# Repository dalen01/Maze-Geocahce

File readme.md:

# Maze Geocache

An electronic maze puzzle inspired by the maze module in *Keep Talking and Nobody Explodes*. A player uses an arcade joystick to move a white light through an invisible maze on a 6×6 RGB LED matrix. Reaching four randomly selected goals in succession triggers a solenoid and opens the geocache.

This repository contains the Arduino firmware, KiCad PCB design and production files, enclosure models, and laser-cutting drawings required to build the project.

## How it works

- The two green LEDs identify which of the nine maze layouts is active.
- The white LED is the player's current position.
- The red LED is the goal.
- The joystick moves the player up, down, left, or right.
- Hitting a wall or the edge of the matrix displays a red cross and resets progress.
- Reaching a goal displays the number of rounds remaining and loads a new random maze.
- Completing four mazes plays a victory animation and energizes the solenoid for 500 ms.

The walls are intentionally not shown on the LED matrix. Players must use an external maze reference or solve the layout by deduction.

## Hardware

The supplied PCB is designed around the following main components:

- Arduino Nano or a pin-compatible board
- 36 × WS2812B addressable RGB LEDs arranged as a 6×6 matrix
- Arcade joystick with four directional switches
- Solenoid lock
- TIP120 Darlington transistor and SS34 flyback diode for solenoid control
- 3 × AA battery holder
- Custom PCB and enclosure

See [`PCB Design/Maze Geocache/production/bom.csv`](PCB%20Design/Maze%20Geocache/production/bom.csv) for the PCB bill of materials and component footprints.

## Pin assignment

| Function | Arduino Nano pin |
| --- | ---: |
| Solenoid control | D2 |
| Joystick up | D3 |
| Joystick down | D4 |
| Joystick right | D5 |
| Joystick left | D6 |
| WS2812B data | D7 |

The directional inputs use the Arduino's internal pull-up resistors and are active low.

## Firmware setup

### Requirements

- Arduino IDE or Arduino CLI
- Arduino AVR Boards package
- [Adafruit NeoPixel](https://github.com/adafruit/Adafruit_NeoPixel) library

### Prepare the sketch

The current sketch contains an absolute Windows path for `MazeWalls.h`. Before compiling on another computer:

1. Copy `Code/MazeWalls.h` into `Code/Maze/`.
2. Change the second line of `Code/Maze/Maze.ino` to:

```cpp
#include "MazeWalls.h"
```

### Upload with Arduino IDE

1. Open `Code/Maze/Maze.ino`.
2. Install **Adafruit NeoPixel** from the Library Manager.
3. Select **Arduino Nano** and the correct processor variant and serial port.
4. Compile and upload the sketch.
5. Optionally open the Serial Monitor at **9600 baud** to view movement and game-state messages.

## Assembly notes

1. Manufacture and populate the PCB from the files in `PCB Design/Maze Geocache/`.
2. Connect the four joystick switches to the matching UP, DOWN, LEFT, and RIGHT JST connectors.
3. Connect the solenoid to the two-pin screw terminal.
4. Install the Arduino Nano with the correct orientation.
5. Fit the PCB, joystick, lock, and battery holder into the enclosure.
6. Test all controls and the lock release before closing the enclosure.

The solenoid is an inductive, relatively high-current load. Do not drive it directly from an Arduino pin. Confirm the solenoid voltage, polarity, current requirement, transistor pinout, flyback-diode orientation, and power-source capability before applying power.

## Repository layout

| Path | Contents |
| --- | --- |
| `Code/` | Arduino sketch and maze wall definitions |
| `PCB Design/` | KiCad schematics, PCB layout, 3D board model, BOM, placement data, and fabrication archive |
| `3D Files/` | Fusion 360 archive and STEP model of the complete enclosure |
| `DXF Files/` | Laser-cutting drawings for the box and acrylic window |

## Customization

- Change `numberToGo` in `Maze.ino` to alter the number of successful mazes required to unlock the cache.
- Adjust the RGB values in `drawGame()` to change marker colors or brightness.
- Edit `circlePos`, `wallsVertical`, and `wallsHorizontal` in `MazeWalls.h` to change or add maze layouts. Update `MAZE_COUNT` when adding or removing layouts.
- Change the 500 ms delay in the victory sequence if the lock needs a different activation time, while staying within the solenoid's safe duty cycle.

## Fabrication warning

Review the PCB, mechanical files, clearances, power design, and production outputs before ordering parts or manufacturing. The repository does not include a verified electrical rating for the solenoid or batteries, and the design files should not be treated as production-ready without an independent check.

## Acknowledgements

The puzzle concept is inspired by the maze module from *Keep Talking and Nobody Explodes*. This is an independent fan project and is not affiliated with or endorsed by Steel Crate Games.

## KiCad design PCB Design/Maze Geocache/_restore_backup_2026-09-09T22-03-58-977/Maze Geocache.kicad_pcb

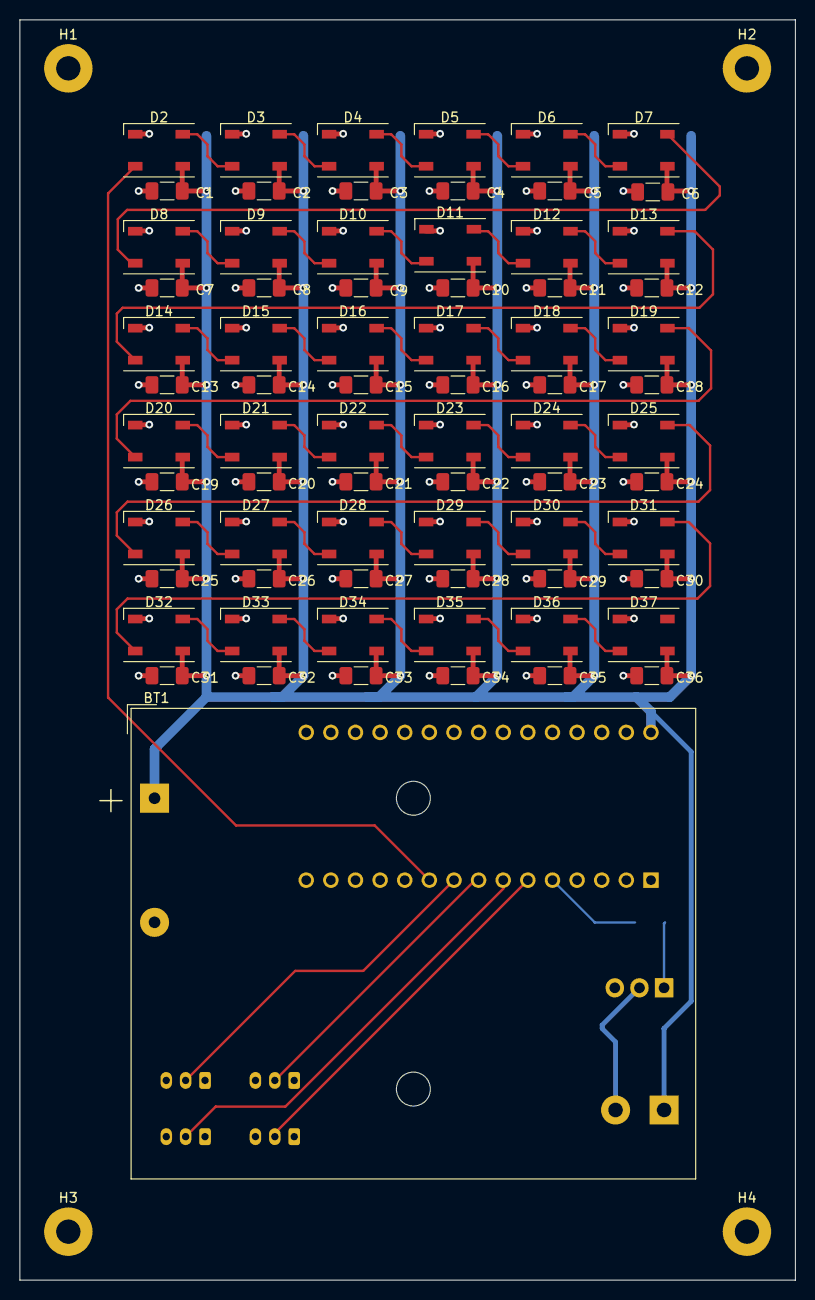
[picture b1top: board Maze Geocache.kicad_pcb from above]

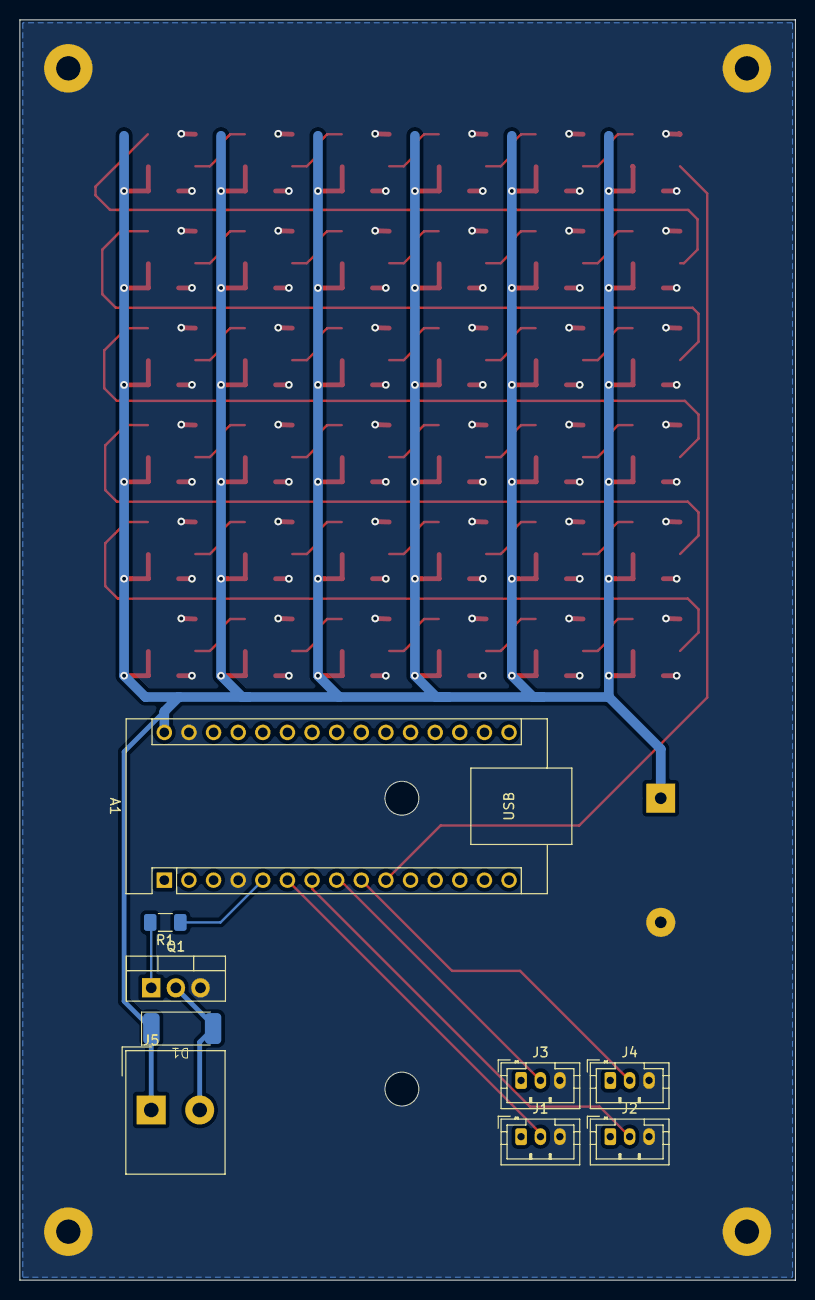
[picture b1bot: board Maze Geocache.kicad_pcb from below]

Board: 2 copper layers, 80.0 x 130.0 mm, 86 parts (9 on the bottom side), 45 nets.

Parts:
A1: Arduino_Nano_v2.x; Arduino_Nano
BT1: Battery; BatteryHolder_TruPower_BH-331P_3xAA
C1, C2, C3, C4, C5, C6, C7, C8, C9, C10, C11, C12, C13, C14, C15, C16, C17, C18, C19, C20, C21, C22, C23, C24, C25, C26, C27, C28, C29, C30, C31, C32, C33, C34, C35, C36: 10pF; C_1206_3216Metric_Pad1.33x1.80mm_HandSolder
D1: SS34
D2, D3, D4, D5, D6, D7, D8, D9, D10, D11, D12, D13, D14, D15, D16, D17, D18, D19, D20, D21, D22, D23, D24, D25, D26, D27, D28, D29, D30, D31, D32, D33, D34, D35, D36, D37: WS2812B; LED_WS2812B_PLCC4_5.0x5.0mm_P3.2mm
H1, H2, H3, H4: MountingHole_Pad; MountingHole_2.5mm_Pad
J1: Joystick connector UP; JST_PH_B3B-PH-K_1x03_P2.00mm_Vertical
J2: Joystick connector DOWN; JST_PH_B3B-PH-K_1x03_P2.00mm_Vertical
J3: Joystick connector RIGHT; JST_PH_B3B-PH-K_1x03_P2.00mm_Vertical
J4: Joystick connector LEFT; JST_PH_B3B-PH-K_1x03_P2.00mm_Vertical
J5: Solenoid; Altech_AK300_1x02_P5.00mm_45-Degree
Q1: TIP120; TO-220-3_Vertical
R1: 220; R_1206_3216Metric_Pad1.30x1.75mm_HandSolder

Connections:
+5V: A1.30 (VIN), BT1.1 (+), C1.2, C2.2, C3.2, C4.2, C5.2, C6.2, C7.2, C8.2, C9.2, C10.2, C11.2, C12.2, C13.2, C14.2, C15.2, C16.2, C17.2, C18.2, C19.2, C20.2, C21.2, C22.2, C23.2, C24.2, C25.2, C26.2, C27.2, C28.2, C29.2, C30.2, C31.2, C32.2, C33.2, C34.2, C35.2, C36.2, D1.2, D2.1 (VDD), D3.1 (VDD), D4.1 (VDD), D5.1 (VDD), D6.1 (VDD), D7.1 (VDD), D8.1 (VDD), D9.1 (VDD), D10.1 (VDD), D11.1 (VDD), D12.1 (VDD), D13.1 (VDD), D14.1 (VDD), D15.1 (VDD), D16.1 (VDD), D17.1 (VDD), D18.1 (VDD), D19.1 (VDD), D20.1 (VDD), D21.1 (VDD), D22.1 (VDD), D23.1 (VDD), D24.1 (VDD), D25.1 (VDD), D26.1 (VDD), D27.1 (VDD), D28.1 (VDD), D29.1 (VDD), D30.1 (VDD), D31.1 (VDD), D32.1 (VDD), D33.1 (VDD), D34.1 (VDD), D35.1 (VDD), D36.1 (VDD), D37.1 (VDD), J5.1
Down_Button: A1.7 (D4), J2.2
GND: A1.4 (GND), A1.29 (GND), BT1.2 (-), C1.1, C2.1, C3.1, C4.1, C5.1, C6.1, C7.1, C8.1, C9.1, C10.1, C11.1, C12.1, C13.1, C14.1, C15.1, C16.1, C17.1, C18.1, C19.1, C20.1, C21.1, C22.1, C23.1, C24.1, C25.1, C26.1, C27.1, C28.1, C29.1, C30.1, C31.1, C32.1, C33.1, C34.1, C35.1, C36.1, D2.3 (VSS), D3.3 (VSS), D4.3 (VSS), D5.3 (VSS), D6.3 (VSS), D7.3 (VSS), D8.3 (VSS), D9.3 (VSS), D10.3 (VSS), D11.3 (VSS), D12.3 (VSS), D13.3 (VSS), D14.3 (VSS), D15.3 (VSS), D16.3 (VSS), D17.3 (VSS), D18.3 (VSS), D19.3 (VSS), D20.3 (VSS), D21.3 (VSS), D22.3 (VSS), D23.3 (VSS), D24.3 (VSS), D25.3 (VSS), D26.3 (VSS), D27.3 (VSS), D28.3 (VSS), D29.3 (VSS), D30.3 (VSS), D31.3 (VSS), D32.3 (VSS), D33.3 (VSS), D34.3 (VSS), D35.3 (VSS), D36.3 (VSS), D37.3 (VSS), H1.1, H2.1, H3.1, H4.1, J1.3, J2.3, J3.3, J4.3, Q1.3 (E)
LED Row 2: D7.2 (DOUT), D8.4 (DIN)
LED Row 3: D13.2 (DOUT), D14.4 (DIN)
LED Row 4: D19.2 (DOUT), D20.4 (DIN)
LED Row 5: D25.2 (DOUT), D26.4 (DIN)
LED Row 6: D31.2 (DOUT), D32.4 (DIN)
Left_Button: A1.9 (D6), J4.2
unnamed: D2.2 (DOUT), D3.4 (DIN)
unnamed: D3.2 (DOUT), D4.4 (DIN)
unnamed: D4.2 (DOUT), D5.4 (DIN)
unnamed: D5.2 (DOUT), D6.4 (DIN)
unnamed: D6.2 (DOUT), D7.4 (DIN)
unnamed: D8.2 (DOUT), D9.4 (DIN)
unnamed: D9.2 (DOUT), D10.4 (DIN)
unnamed: D10.2 (DOUT), D11.4 (DIN)
unnamed: D11.2 (DOUT), D12.4 (DIN)
unnamed: D12.2 (DOUT), D13.4 (DIN)
unnamed: D14.2 (DOUT), D15.4 (DIN)
unnamed: D15.2 (DOUT), D16.4 (DIN)
unnamed: D16.2 (DOUT), D17.4 (DIN)
unnamed: D17.2 (DOUT), D18.4 (DIN)
unnamed: D18.2 (DOUT), D19.4 (DIN)
unnamed: D20.2 (DOUT), D21.4 (DIN)
unnamed: D21.2 (DOUT), D22.4 (DIN)
unnamed: D22.2 (DOUT), D23.4 (DIN)
unnamed: D23.2 (DOUT), D24.4 (DIN)
unnamed: D24.2 (DOUT), D25.4 (DIN)
unnamed: D26.2 (DOUT), D27.4 (DIN)
unnamed: D27.2 (DOUT), D28.4 (DIN)
unnamed: D28.2 (DOUT), D29.4 (DIN)
unnamed: D29.2 (DOUT), D30.4 (DIN)
unnamed: D30.2 (DOUT), D31.4 (DIN)
unnamed: D32.2 (DOUT), D33.4 (DIN)
unnamed: D33.2 (DOUT), D34.4 (DIN)
unnamed: D34.2 (DOUT), D35.4 (DIN)
unnamed: D35.2 (DOUT), D36.4 (DIN)
unnamed: D36.2 (DOUT), D37.4 (DIN)
unnamed: D1.1, J5.2, Q1.2 (C)
unnamed: Q1.1 (B), R1.2
Right_Button: A1.8 (D5), J3.2
S_ctrl: A1.5 (D2), R1.1
Up_Button: A1.6 (D3), J1.2
WS2812 D_in: A1.10 (D7), D2.4 (DIN)

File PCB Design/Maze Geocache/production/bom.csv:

Designator,Footprint,Quantity,Value,LCSC Part #
A1,Arduino_Nano,1,Arduino_Nano_v2.x,
BT1,BatteryHolder_TruPower_BH-331P_3xAA,1,Battery,
"C1, C10, C11, C12, C13, C14, C15, C16, C17, C18, C19, C2, C20, C21, C22, C23, C24, C25, C26, C27, C28, C29, C3, C30, C31, C32, C33, C34, C35, C36, C4, C5, C6, C7, C8, C9",1206,36,10pF,
D1,SS34,1,SS34,
"D10, D11, D12, D13, D14, D15, D16, D17, D18, D19, D2, D20, D21, D22, D23, D24, D25, D26, D27, D28, D29, D3, D30, D31, D32, D33, D34, D35, D36, D37, D4, D5, D6, D7, D8, D9",LED_WS2812B_PLCC4_5.0x5.0mm_P3.2mm,36,WS2812B,
"H1, H2, H3, H4",MountingHole_2.5mm_Pad,4,MountingHole_Pad,
J1,JST_PH_B3B-PH-K_1x03_P2.00mm_Vertical,1,Joystick connector UP,
J2,JST_PH_B3B-PH-K_1x03_P2.00mm_Vertical,1,Joystick connector DOWN,
J3,JST_PH_B3B-PH-K_1x03_P2.00mm_Vertical,1,Joystick connector RIGHT,
J4,JST_PH_B3B-PH-K_1x03_P2.00mm_Vertical,1,Joystick connector LEFT,
J5,Altech_AK300_1x02_P5.00mm_45-Degree,1,Solenoid,
Q1,TO-220-3_Vertical,1,TIP120,
R1,1206,1,220,

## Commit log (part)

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2024-03-19 Add .gitignore file to ignore .vscode directory
2024-03-19 Add readme file
2024-03-19 Refactor Arduino code for "Keep Talking and Nobody Explodes" geocache
2024-03-19 Update geocache code with additional equipment list
2024-03-21 Add maze functionality and update maze walls
